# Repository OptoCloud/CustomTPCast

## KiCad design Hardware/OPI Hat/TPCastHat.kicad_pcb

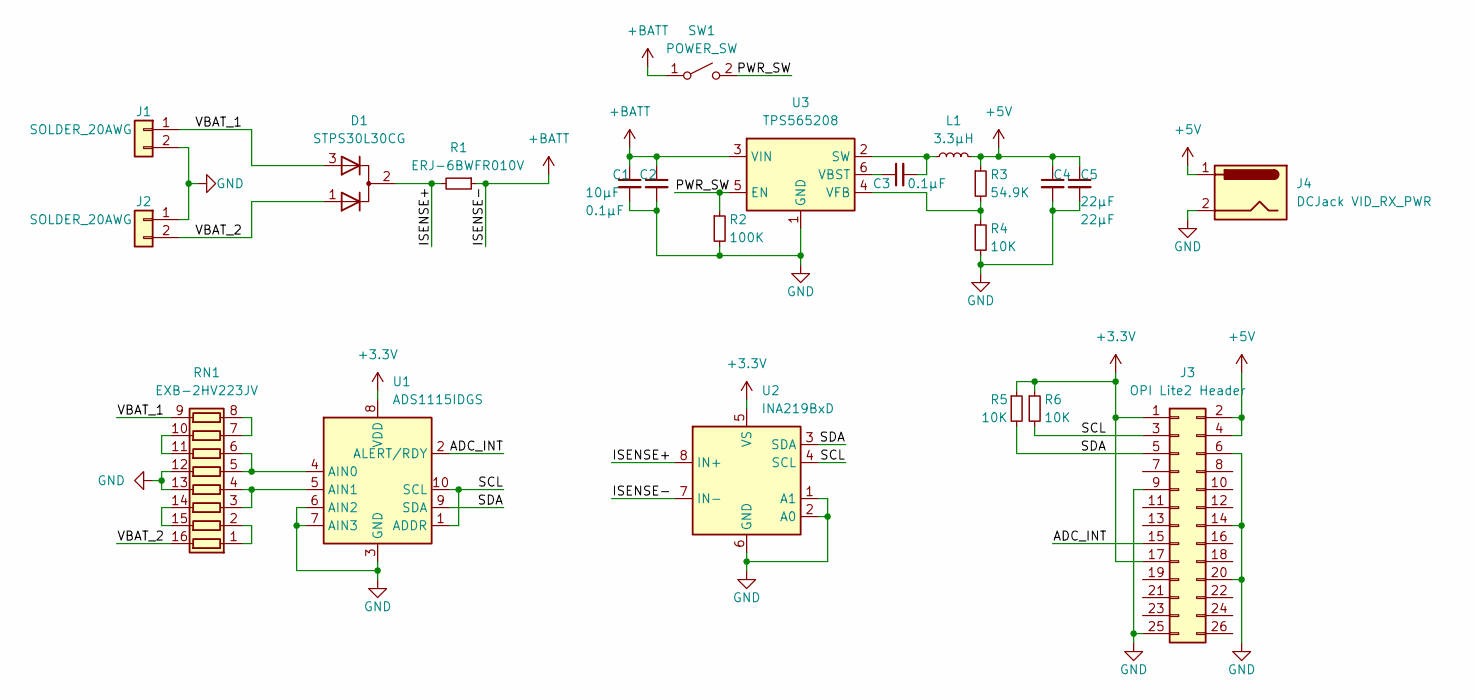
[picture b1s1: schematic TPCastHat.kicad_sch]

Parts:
C1: 10µF; C_0805_2012Metric
C2, C3: 0.1µF; C_0805_2012Metric
C4, C5: 22µF; C_0805_2012Metric
D1: STPS30L30CG
J1, J2: SOLDER_20AWG; SolderWire-0.25sqmm_1x02_P4.5mm_D0.65mm_OD2mm_Relief2x
J3: OPI Lite2 Header; PinSocket_2x13_P2.54mm_Vertical
J4: DCJack VID_RX_PWR
L1: 3.3µH; C_0805_2012Metric
R1: ERJ-6BWFR010V; R_1206_3216Metric
R2: 100K; R_0805_2012Metric
R3: 54.9K; R_0805_2012Metric
R4, R5, R6: 10K; R_0805_2012Metric
RN1: EXB-2HV223JV; RESCAXE50P380X160X55-16N
SW1: POWER_SW
U1: ADS1115IDGS; TSSOP-10_3x3mm_P0.5mm
U2: INA219BxD; SOIC-8_3.9x4.9mm_P1.27mm
U3: TPS565208; SOT-23-6

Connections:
+3V3: J3.1, J3.17, R5.1, R6.1, U1.8 (VDD), U2.5 (VS)
+5V: C4.1, C5.1, J3.2, J3.4, J4.1, L1.2, R3.1
+BATT: C1.1, C2.1, R1.1, SW1.1 (A), U2.7 (IN-), U3.3 (VIN)
/ADC_INT: J3.15, U1.2 (ALERT/RDY)
/ISENSE+: D1.2 (A), R1.2, U2.8 (IN+)
/PWR_SW: R2.1, SW1.2 (B), U3.5 (EN)
/SCL: J3.3, R6.2, U1.1 (ADDR), U1.10 (SCL), U2.4 (SCL)
/SDA: J3.5, R5.2, U1.9 (SDA), U2.3 (SDA)
/VBAT_1: D1.3 (K), J1.1, RN1.9 (R8.2)
/VBAT_2: D1.1 (K), J2.2, RN1.16 (R1.2)
GND: C1.2, C2.2, C4.2, C5.2, J1.2, J2.1, J3.6, J3.9, J3.14, J3.20, J3.25, J4.2, R2.2, R4.2, RN1.12 (R5.2), RN1.13 (R4.2), U1.3 (GND), U1.6 (AIN2), U1.7 (AIN3), U2.1 (A1), U2.2 (A0), U2.6 (GND), U3.1 (GND)
unnamed: C3.1, U3.6 (VBST)
unnamed: C3.2, L1.1, U3.2 (SW)
unnamed: R3.2, R4.1, U3.4 (VFB)
unnamed: RN1.1 (R1.1), RN1.2 (R2.1)
unnamed: RN1.3 (R3.1), RN1.4 (R4.1), U1.5 (AIN1)
unnamed: RN1.5 (R5.1), RN1.6 (R6.1), U1.4 (AIN0)
unnamed: RN1.7 (R7.1), RN1.8 (R8.1)
unnamed: RN1.10 (R7.2), RN1.11 (R6.2)
unnamed: RN1.14 (R3.2), RN1.15 (R2.2)

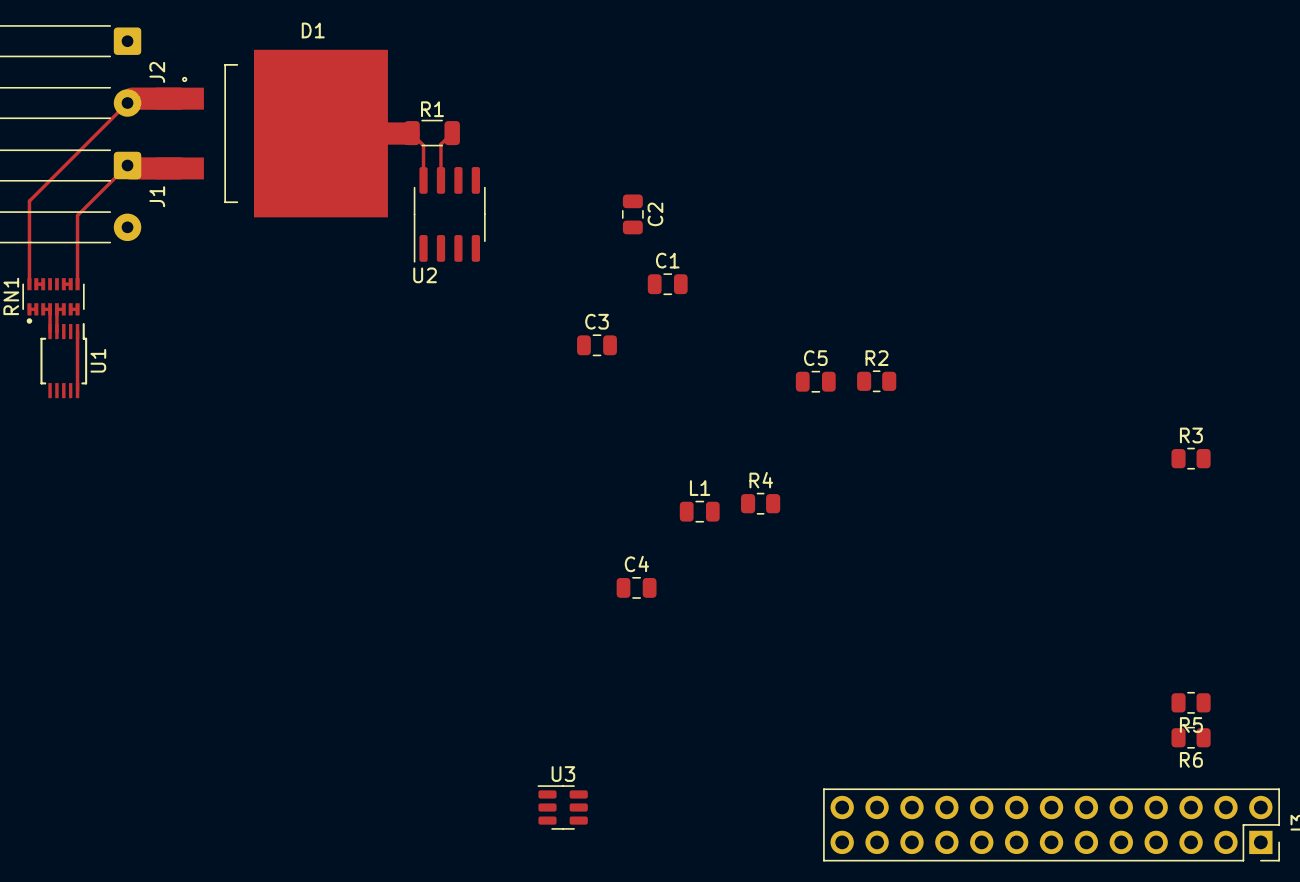
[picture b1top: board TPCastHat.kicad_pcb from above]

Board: 2 copper layers, 20 parts (0 on the bottom side), 20 nets.

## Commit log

2022-02-28 Organize into folders
2022-02-28 Upload blender file
2022-03-01 More changes to pcb design
